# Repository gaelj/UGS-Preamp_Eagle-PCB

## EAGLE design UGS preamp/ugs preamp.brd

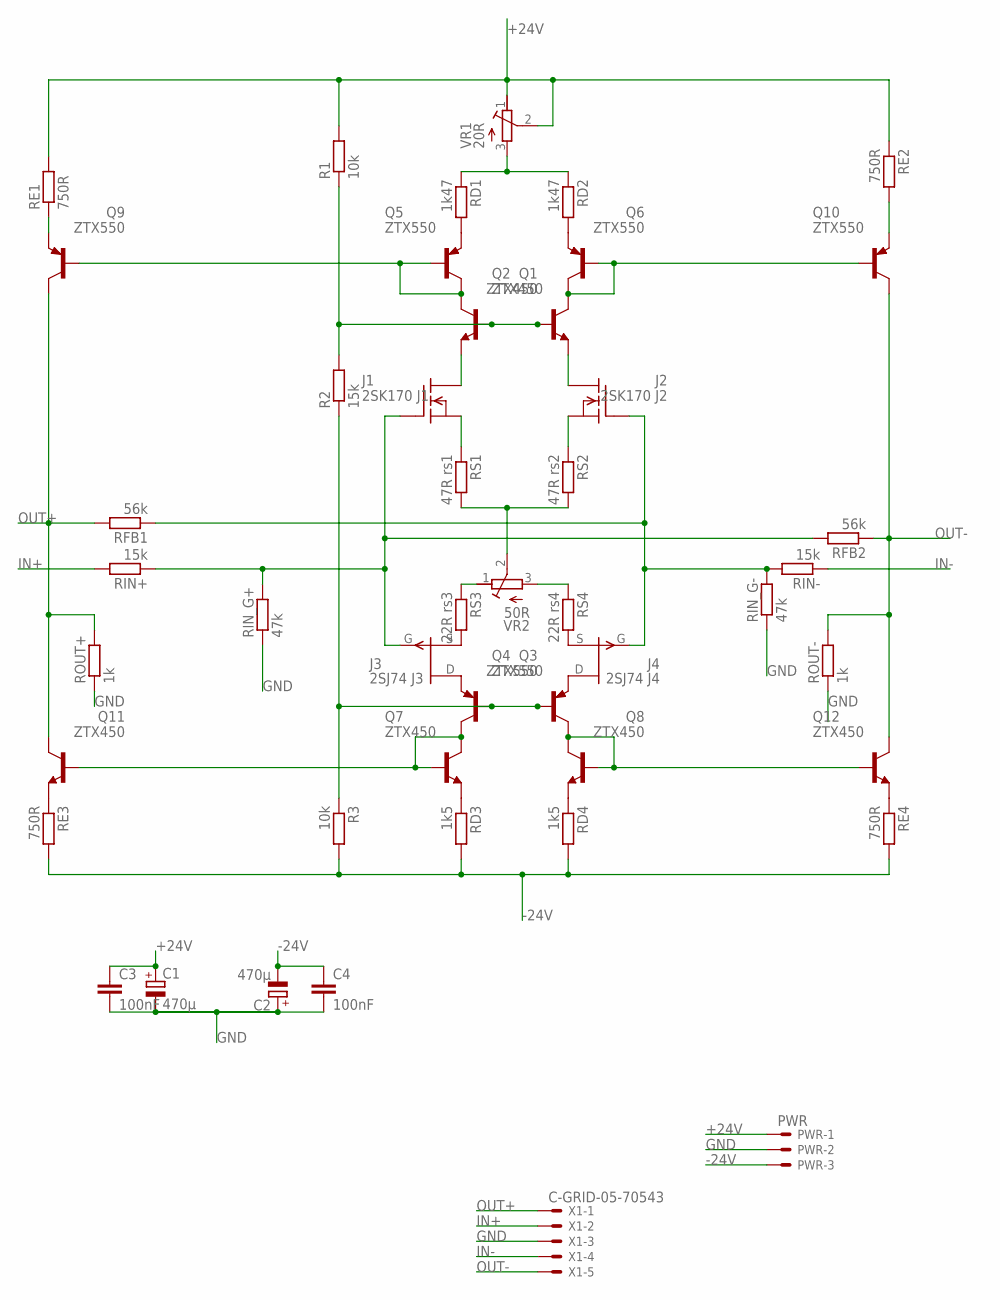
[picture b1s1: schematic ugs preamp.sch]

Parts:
C1, C2: 470µ; E7,5-16
C3, C4: 100nF; C050-025X075
J1: 2SK170 J1; TO92
J2: 2SK170 J2; TO92
J3: 2SJ74 J3; TO92
J4: 2SJ74 J4; TO92
PWR: PWR; 70543-03
Q1, Q2, Q7, Q8, Q11, Q12: ZTX450; TO92-EBC
Q3, Q4, Q5, Q6, Q9, Q10: ZTX550; TO92-EBC
R1, R3: 10k; 0207/10
R2: 15k; 0207/10
RD1, RD2: 1k47; 0207/10
RD3, RD4: 1k5; 0207/10
RE1, RE2, RE3, RE4: 750R; 0207/10
RFB1, RFB2: 56k; 0207/10
RIN+: 15k; 0207/10
RIN-: 15k; 0207/10
RIN_G+: 47k; 0207/10
RIN_G-: 47k; 0207/10
ROUT+: 1k; 0207/10
ROUT-: 1k; 0207/10
RS1: 47R rs1; 0207/10
RS2: 47R rs2; 0207/10
RS3: 22R rs3; 0207/10
RS4: 22R rs4; 0207/10
VR1: 20R; RTRIMT93YA
VR2: 50R; RTRIMT93YA
X1: C-GRID-05-70543; 70543-05

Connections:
+24V: C1.+, C3.1, PWR.1, R1.2, RE1.2, RE2.1, VR1.1 (E), VR1.2 (S)
-24V: C2.-, C4.1, PWR.3, R3.2, RD3.2, RD4.2, RE3.2, RE4.2
GND: C1.-, C2.+, C3.2, C4.2, PWR.2, RIN_G+.1, RIN_G-.1, ROUT+.1, ROUT-.1, X1.3
IN+: RIN+.2, X1.2
IN-: RIN-.1, X1.4
unnamed: J3.3 (D), Q3.E
unnamed: RD1.1, RD2.1, VR1.3 (A)
unnamed: Q1.B, Q2.B, R1.1, R2.2
unnamed: Q3.B, Q4.B, R2.1, R3.1
unnamed: J4.3 (D), Q4.E
unnamed: J4.1 (S), RS4.2
unnamed: J3.1 (S), RS3.2
unnamed: Q10.E, RE2.2
unnamed: J2.2 (G), J4.2 (G), RFB1.1, RIN-.2, RIN_G-.2
unnamed: RS1.2, RS2.2, VR2.2 (S)
unnamed: J2.1 (S), RS2.1
unnamed: Q5.E, RD1.2
unnamed: J1.1 (S), RS1.1
unnamed: RS3.1, VR2.1 (E)
unnamed: RS4.1, VR2.3 (A)
unnamed: J1.2 (G), J3.2 (G), RFB2.2, RIN+.1, RIN_G+.2
unnamed: Q6.E, RD2.2
unnamed: Q11.E, RE3.1
unnamed: Q9.E, RE1.1
unnamed: Q8.E, RD4.1
unnamed: Q4.C, Q8.B, Q8.C, Q12.B
unnamed: Q7.E, RD3.1
unnamed: Q12.E, RE4.1
unnamed: Q2.C, Q6.B, Q6.C, Q10.B
unnamed: Q3.C, Q7.B, Q7.C, Q11.B
unnamed: J1.3 (D), Q1.E
unnamed: J2.3 (D), Q2.E
unnamed: Q1.C, Q5.B, Q5.C, Q9.B
OUT+: Q9.C, Q11.C, RFB1.2, ROUT+.2, X1.1
OUT-: Q10.C, Q12.C, RFB2.1, ROUT-.2, X1.5

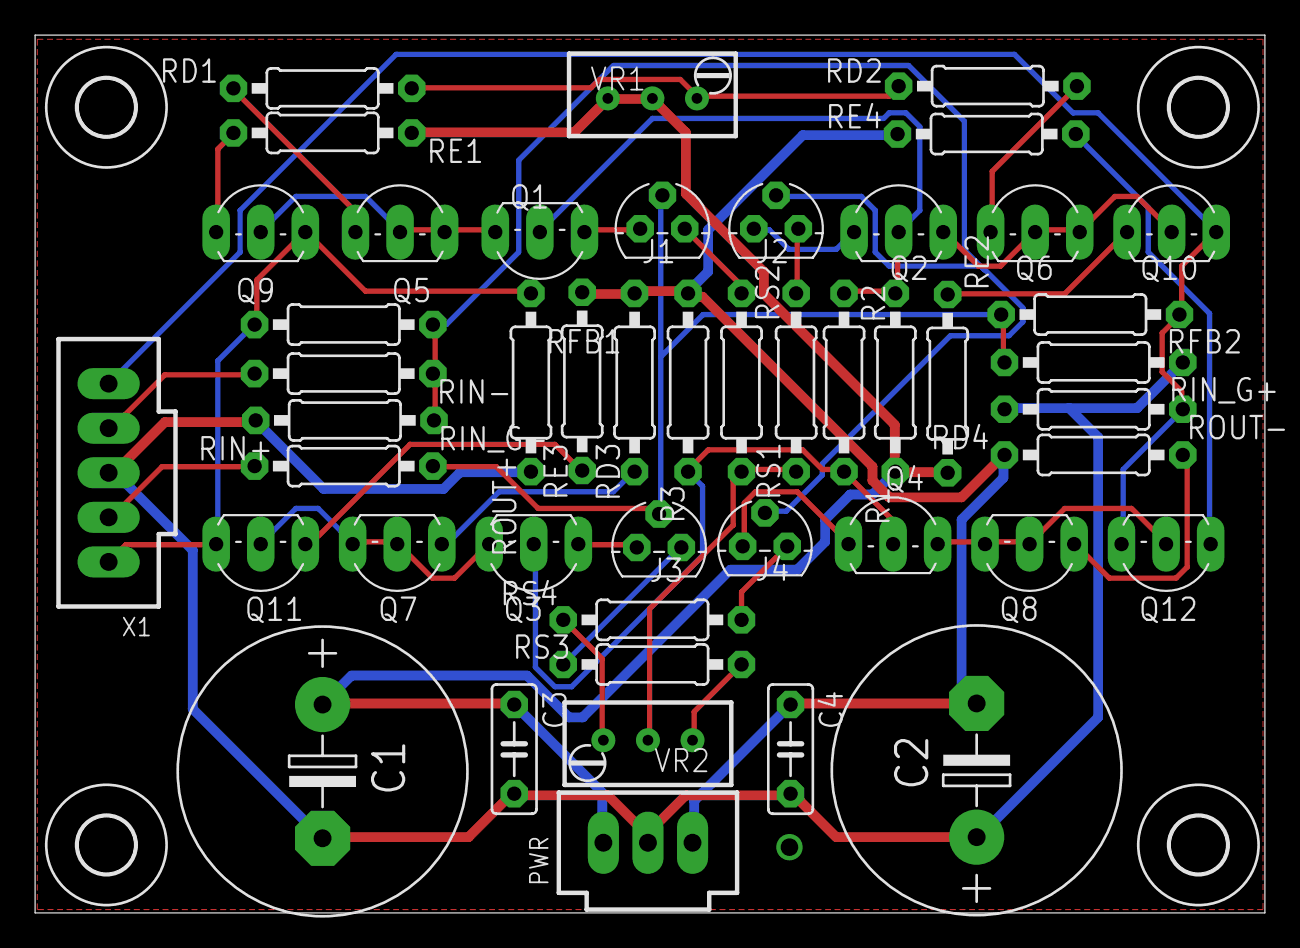
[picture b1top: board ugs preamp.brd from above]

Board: 2 copper layers, 70.1 x 50.0 mm, 51 parts (0 on the bottom side), 35 nets.

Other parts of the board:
U$1, U$2, U$3, U$4: 3,2

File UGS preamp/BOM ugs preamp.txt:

Qty	Value	Device	Package	Parts	Description
2	10k	R-EU_0207/10	0207/10	R1, R3	RESISTOR, European symbol
3	15k	R-EU_0207/10	0207/10	R2, RIN+, RIN-	RESISTOR, European symbol
2	1k	R-EU_0207/10	0207/10	ROUT+, ROUT-	RESISTOR, European symbol
2	1k47	R-EU_0207/10	0207/10	RD1, RD2	RESISTOR, European symbol
2	1k5	R-EU_0207/10	0207/10	RD3, RD4	RESISTOR, European symbol
1	20R	R-TRIMMT93YA	RTRIMT93YA	VR1	Trimm resistor
2	22R	R-EU_0207/10	0207/10	RS3, RS4	RESISTOR, European symbol
2	2SJ74	2N3820	TO92	J3, J4	P-Channel Junction FET
2	2SK170	BSS101	TO92	J1, J2	"N-Channel Enhancement MOSFET 200V; 0,16A; 11Ohm"
2	470µ	CPOL-EUE5-13	E5-13	C1, C2	POLARIZED CAPACITOR, European symbol
2	47R	R-EU_0207/10	0207/10	RS1, RS2	RESISTOR, European symbol
2	47k	R-EU_0207/10	0207/10	RIN_G+, RIN_G-	RESISTOR, European symbol
1	50R	R-TRIMMT93YA	RTRIMT93YA	VR2	Trimm resistor
2	56k	R-EU_0207/10	0207/10	RFB1, RFB2	RESISTOR, European symbol
4	750R	R-EU_0207/10	0207/10	RE1, RE2, RE3, RE4	RESISTOR, European symbol
1	C-GRID-05-70543	C-GRID-05-70543	70543-05	X1	CONNECTOR
1	PWR	C-GRID-03-70543	70543-03	PWR	CONNECTOR
6	ZTX450	-NPN-TO92-EBC	TO92-EBC	Q1, Q2, Q7, Q8, Q11, Q12	NPN Transistror
6	ZTX550	BC328-16-PNP-TO92-EBC	TO92-EBC	Q3, Q4, Q5, Q6, Q9, Q10	PNP Transistror

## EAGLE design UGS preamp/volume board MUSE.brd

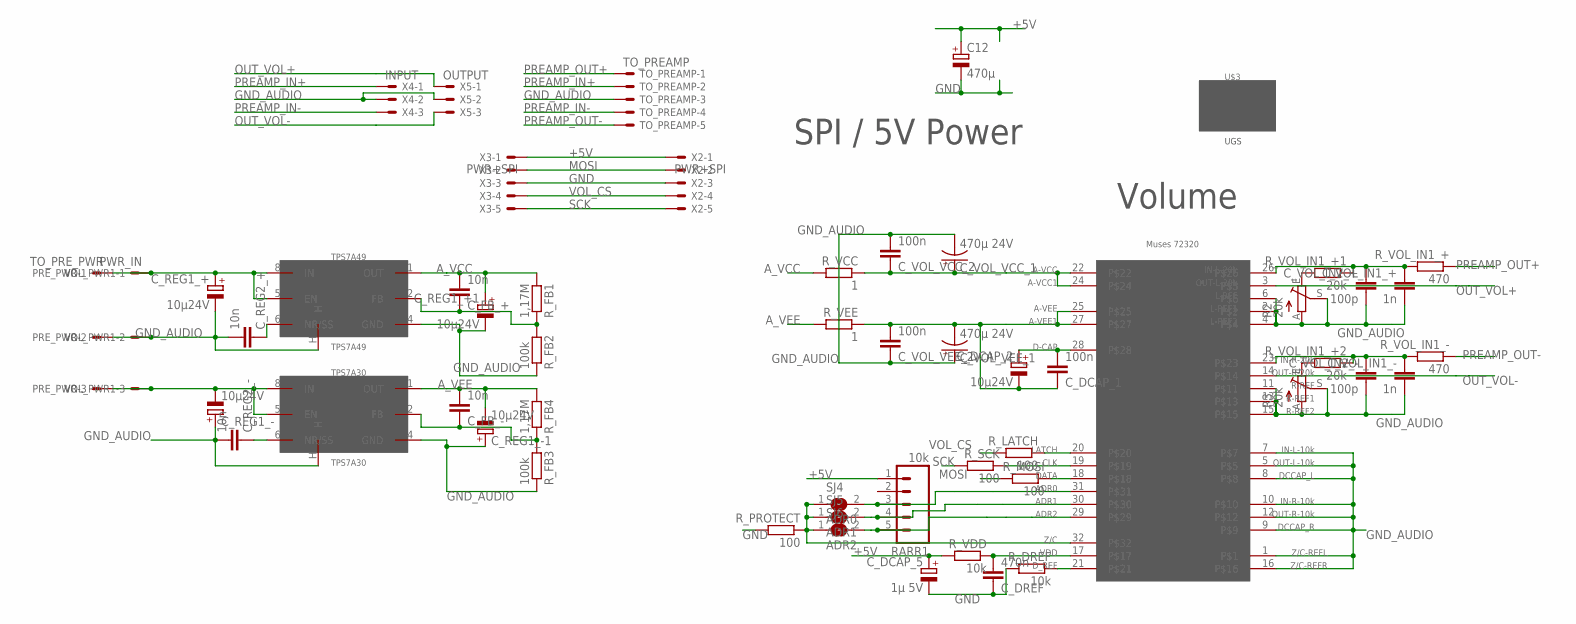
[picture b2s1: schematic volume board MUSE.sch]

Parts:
C12: 470µ; E2,5-6
C_DCAP_1: 100n; C0603
C_DCAP_2: 10µ24V; PANASONIC_C
C_DCAP_5: 1µ 5V; E1,8-4
C_DREF: 470n; C075-042X103
C_FB_+: 10n; C0603
C_FB_-: 10n; C0603
C_REG1_+, C_REG1_+1, C_REG1_-, C_REG1_-1: 10µ24V; PANASONIC_C
C_REG2_+, C_REG2_-: 10n; C0603
C_VOL_IN1_+, C_VOL_IN1_-: 1n; C102-043X133
C_VOL_IN2_+, C_VOL_IN2_-: 100p; C075-032X103
C_VOL_VCC_1: 470µ 24V; PANASONIC_H13
C_VOL_VCC_2: 100n; C0603
C_VOL_VEE_1: 470µ 24V; PANASONIC_H13
C_VOL_VEE_2: 100n; C0603
PRE_PWR: TO_PRE_PWR; 70543-03
R2, R3: 20k; RJ9W
RARR1: 10k; 1X05
R_DREF: 10k; 0207/7
R_FB1, R_FB4: 1,17M; 0207/7
R_FB2, R_FB3: 100k; 0207/7
R_LATCH: 100; 0207/7
R_MOSI: 100; 0207/7
R_PROTECT: 100; 0207/7
R_SCK: 100; 0207/7
R_VCC: 1; 0207/7
R_VDD: 10k; 0207/7
R_VEE: 1; 0207/7
R_VOL_IN1_+, R_VOL_IN1_-: 470; 0207/10
R_VOL_IN1_+1, R_VOL_IN1_+2: 20k; 0207/7
SJ4: ADR0; SJ
SJ5: ADR1; SJ
SJ6: ADR2; SJ
TO_PREAMP: TO_PREAMP; 70543-05
TPS7A30: TPS7A30; MSOP8
TPS7A49: TPS7A49; MSOP8
U$1: MUSES72320; SSOP32
U$3: UGS
VOL_PWR1: PWR_IN; 70543-03
X2, X3: PWR+SPI; 70543-05
X4: INPUT; 70543-03
X5: OUTPUT; 70543-03

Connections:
+5V: C12.+, C_DCAP_5.+, RARR1.1, R_VDD.2, X2.1, X3.1
A_VCC: C_FB_+.2, C_REG1_+1.+, R_FB1.2, R_VCC.2, TPS7A49.1 (OUT)
A_VEE: C_FB_-.2, C_REG1_-1.-, R_FB4.2, R_VEE.2, TPS7A30.1 (OUT)
GND: C12.-, C_DCAP_5.-, C_DREF.1, R_DREF.2, R_PROTECT.2, X2.3, X3.3
GND_AUDIO: C_REG1_+.-, C_REG1_+1.-, C_REG1_-.+, C_REG1_-1.+, C_REG2_+.2, C_REG2_-.2, C_VOL_IN1_+.2, C_VOL_IN1_-.2, C_VOL_IN2_+.2, C_VOL_IN2_-.2, C_VOL_VCC_1.-, C_VOL_VCC_2.2, C_VOL_VEE_1.+, C_VOL_VEE_2.1, PRE_PWR.2, R2.A, R2.S, R3.A, R3.S, R_FB2.1, R_FB3.1, TO_PREAMP.3, TPS7A30.4 (GND), TPS7A30.H, TPS7A49.4 (GND), TPS7A49.H, U$1.1, U$1.2, U$1.4, U$1.5, U$1.6, U$1.7, U$1.8, U$1.9, U$1.10, U$1.11, U$1.12, U$1.13, U$1.15, U$1.16, VOL_PWR1.2, X4.2, X5.2
JHGCD: R_PROTECT.1, SJ4.1, SJ5.1, SJ6.1, U$1.32
MOSI: R_MOSI.2, X2.2, X3.2
unnamed: RARR1.3, SJ4.2, U$1.31
unnamed: RARR1.5, SJ6.2, U$1.29
unnamed: C_REG1_-.-, PRE_PWR.3, TPS7A30.5 (EN), TPS7A30.8 (IN), VOL_PWR1.3
unnamed: C_VOL_IN1_+.1, C_VOL_IN2_+.1, R_VOL_IN1_+.2, R_VOL_IN1_+1.1, U$1.26
unnamed: C_REG1_+.+, PRE_PWR.1, TPS7A49.5 (EN), TPS7A49.8 (IN), VOL_PWR1.1
unnamed: C_VOL_IN1_-.1, C_VOL_IN2_-.1, R_VOL_IN1_+2.1, R_VOL_IN1_-.2, U$1.23
unnamed: R2.E, R_VOL_IN1_+1.2
unnamed: R3.E, R_VOL_IN1_+2.2
unnamed: C_VOL_VCC_1.+, C_VOL_VCC_2.1, R_VCC.1, U$1.22, U$1.24
unnamed: C_DCAP_1.1, C_DCAP_2.-, C_VOL_VEE_1.-, C_VOL_VEE_2.2, R_VEE.1, U$1.25, U$1.27
unnamed: C_DCAP_1.2, C_DCAP_2.+, U$1.28
unnamed: R_LATCH.1, U$1.20
unnamed: R_SCK.1, U$1.19
unnamed: R_MOSI.1, U$1.18
unnamed: RARR1.4, SJ5.2, U$1.30
unnamed: C_DREF.2, R_VDD.1, U$1.17
unnamed: R_DREF.1, U$1.21
unnamed: C_FB_+.1, R_FB1.1, R_FB2.2, TPS7A49.2 (FB)
unnamed: C_FB_-.1, R_FB3.2, R_FB4.1, TPS7A30.2 (FB)
unnamed: C_REG2_-.1, TPS7A30.6 (NR/SS)
unnamed: C_REG2_+.1, TPS7A49.6 (NR/SS)
OUT_VOL+: U$1.3, X5.1
OUT_VOL-: U$1.14, X5.3
PREAMP_IN+: TO_PREAMP.2, X4.1
PREAMP_IN-: TO_PREAMP.4, X4.3
PREAMP_OUT+: R_VOL_IN1_+.1, TO_PREAMP.1
PREAMP_OUT-: R_VOL_IN1_-.1, TO_PREAMP.5
SCK: R_SCK.2, X2.5, X3.5
VOL_CS: R_LATCH.2, X2.4, X3.4

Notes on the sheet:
Volume
SPI / 5V Power

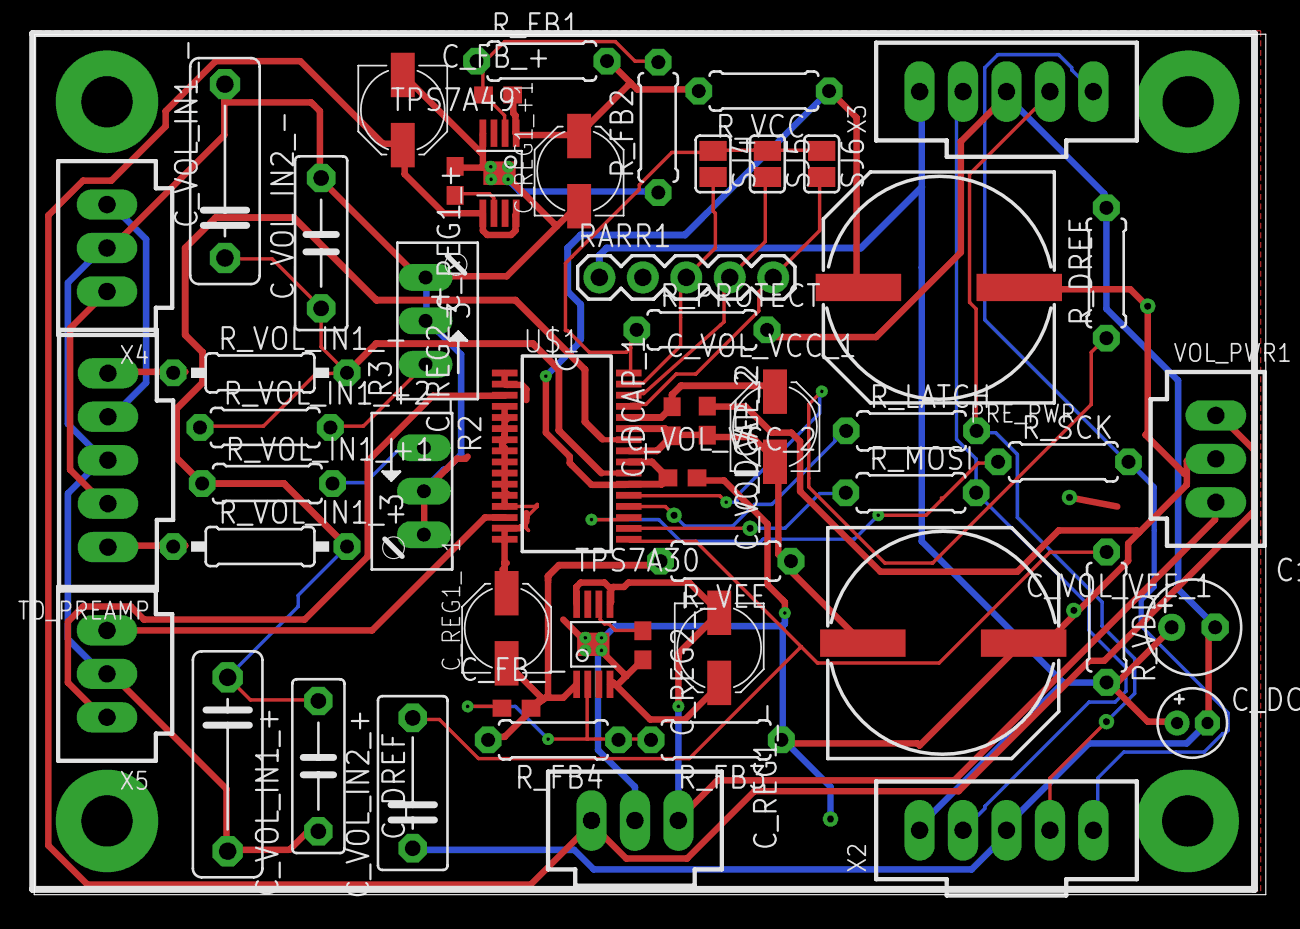
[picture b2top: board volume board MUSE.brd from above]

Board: 2 copper layers, 72.0 x 50.3 mm, 54 parts (0 on the bottom side), 36 nets.

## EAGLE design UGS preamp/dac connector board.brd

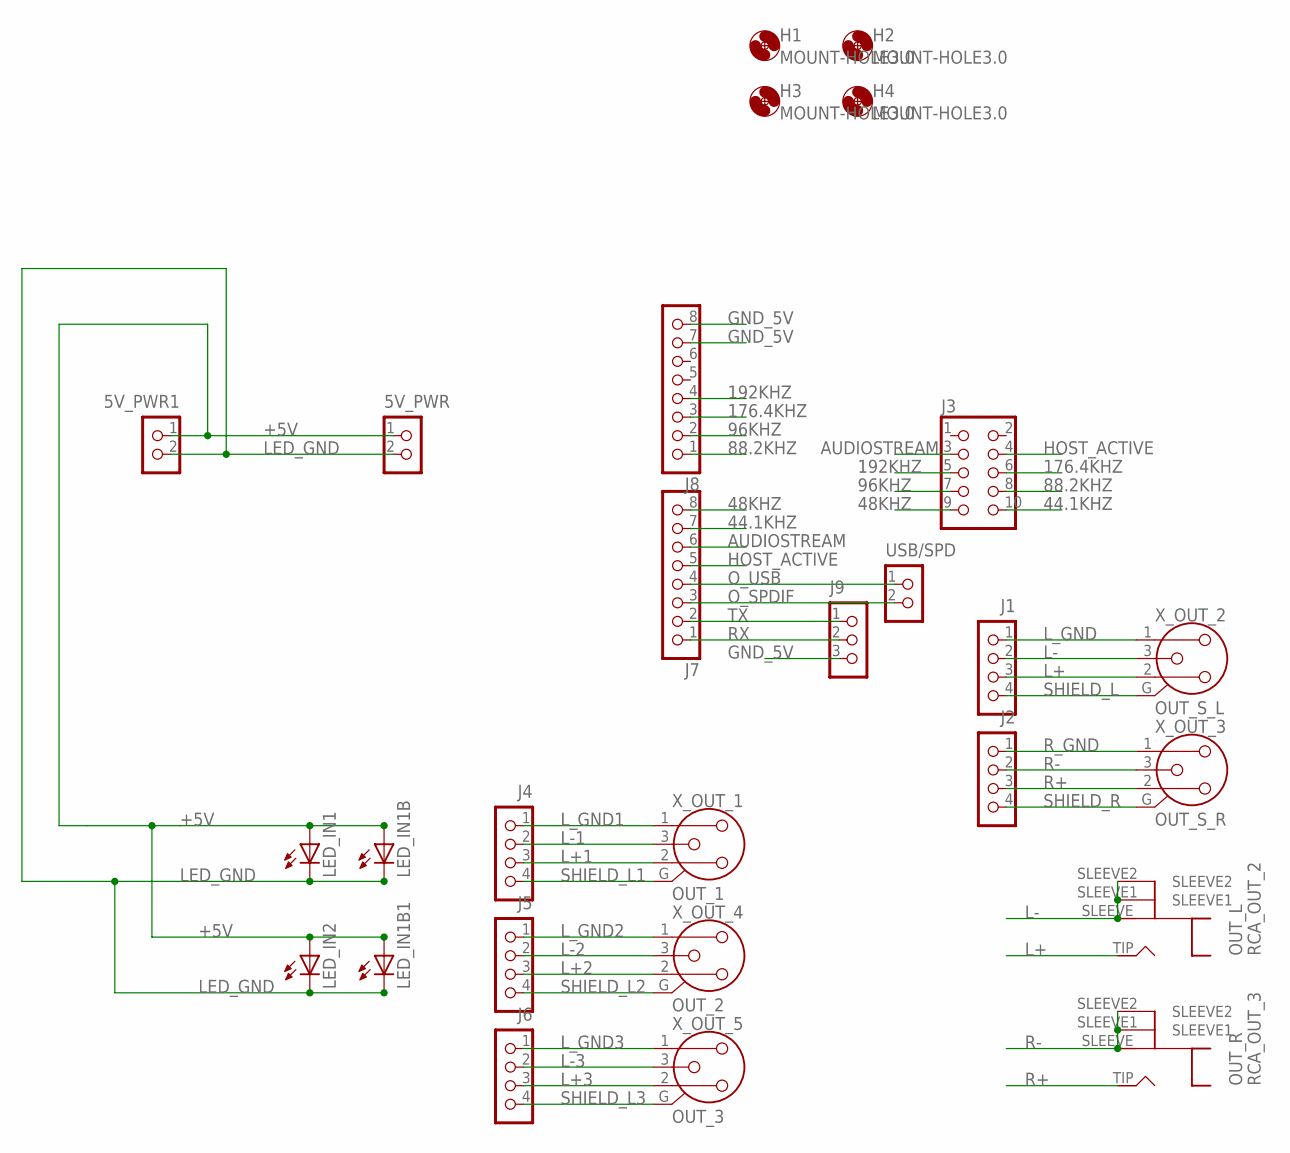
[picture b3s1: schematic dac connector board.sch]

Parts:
5V_PWR, 5V_PWR1: 5V PWR; M1X2
H1, H2, H3, H4: MOUNT-HOLE3.0; 3,0
J1, J2: CON_HEADER_1X04; M1X4
J3: DAC; M2X5
J4: CON_OUT_1; M1X4
J5: CON_OUT_2; M1X4
J6: CON_OUT_3; M1X4
J7: ARD1; M1X8
J8: ARD2; M1X8
J9: SERIAL; M1X3
LED_IN1, LED_IN1B, LED_IN1B1, LED_IN2: TLLG4400; LED3MM
RCA_OUT_2: OUT_L; MONO_JACK
RCA_OUT_3: OUT_R; MONO_JACK
USB/SPD: IN_SEL; M1X2
X_OUT_1: OUT_1; NC3MBH; MPN NC3MBH
X_OUT_2: OUT_S_L; NC3MBH; MPN NC3MBH
X_OUT_3: OUT_S_R; NC3MBH; MPN NC3MBH
X_OUT_4: OUT_2; NC3MBH; MPN NC3MBH
X_OUT_5: OUT_3; NC3MBH; MPN NC3MBH

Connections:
44.1KHZ: J3.10, J7.7
48KHZ: J3.9, J7.8
88.2KHZ: J3.8, J8.1
96KHZ: J3.7, J8.2
176.4KHZ: J3.6, J8.3
192KHZ: J3.5, J8.4
+5V: 5V_PWR.1, 5V_PWR1.1, LED_IN1.A, LED_IN1B.A, LED_IN1B1.A, LED_IN2.A
AUDIOSTREAM: J3.3, J7.6
GND_5V: J8.7, J8.8, J9.3
HOST_ACTIVE: J3.4, J7.5
L+: J1.3, RCA_OUT_2.TIP, X_OUT_2.2
L+1: J4.3, X_OUT_1.2
L+2: J5.3, X_OUT_4.2
L+3: J6.3, X_OUT_5.2
L-: J1.2, RCA_OUT_2.SLEEVE, RCA_OUT_2.SLEEVE1, RCA_OUT_2.SLEEVE2, X_OUT_2.3
L-1: J4.2, X_OUT_1.3
L-2: J5.2, X_OUT_4.3
L-3: J6.2, X_OUT_5.3
LED_GND: 5V_PWR.2, 5V_PWR1.2, LED_IN1.K (C), LED_IN1B.K (C), LED_IN1B1.K (C), LED_IN2.K (C)
L_GND: J1.1, X_OUT_2.1
L_GND1: J4.1, X_OUT_1.1
L_GND2: J5.1, X_OUT_4.1
L_GND3: J6.1, X_OUT_5.1
O_SPDIF: J7.3, USB/SPD.2
O_USB: J7.4, USB/SPD.1
R+: J2.3, RCA_OUT_3.TIP, X_OUT_3.2
R-: J2.2, RCA_OUT_3.SLEEVE, RCA_OUT_3.SLEEVE1, RCA_OUT_3.SLEEVE2, X_OUT_3.3
RX: J7.1, J9.2
R_GND: J2.1, X_OUT_3.1
SHIELD_L: J1.4, X_OUT_2.G
SHIELD_L1: J4.4, X_OUT_1.G
SHIELD_L2: J5.4, X_OUT_4.G
SHIELD_L3: J6.4, X_OUT_5.G
SHIELD_R: J2.4, X_OUT_3.G
TX: J7.2, J9.1

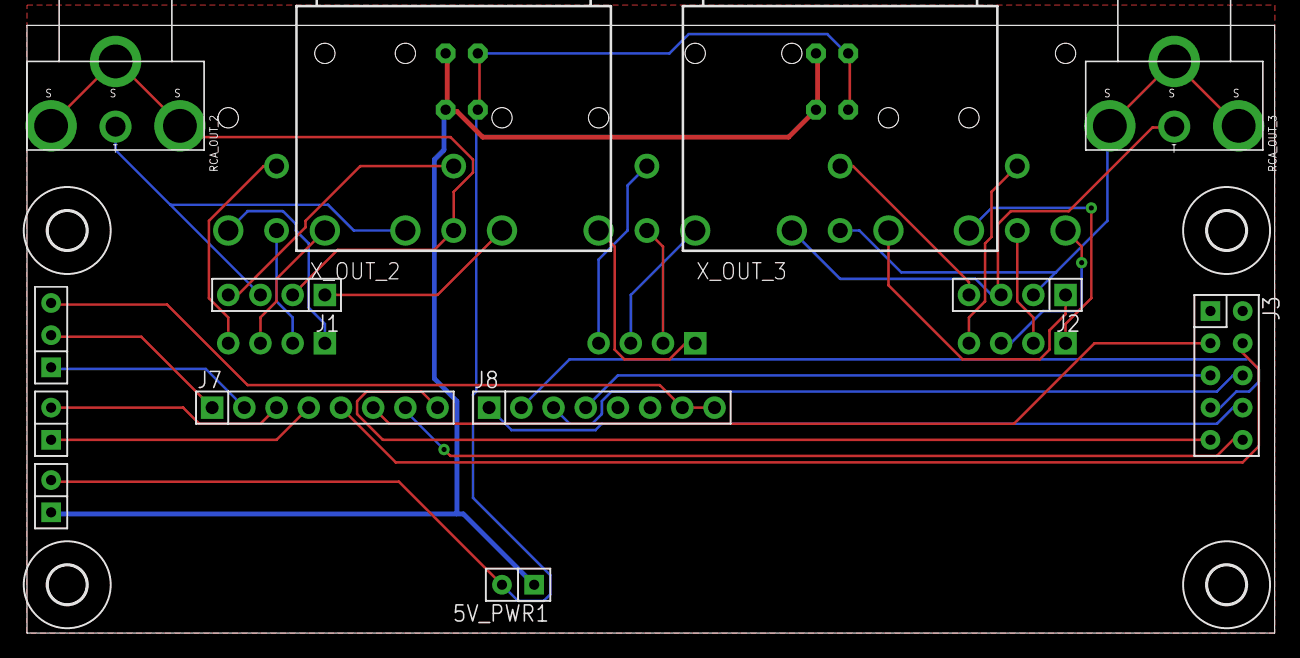
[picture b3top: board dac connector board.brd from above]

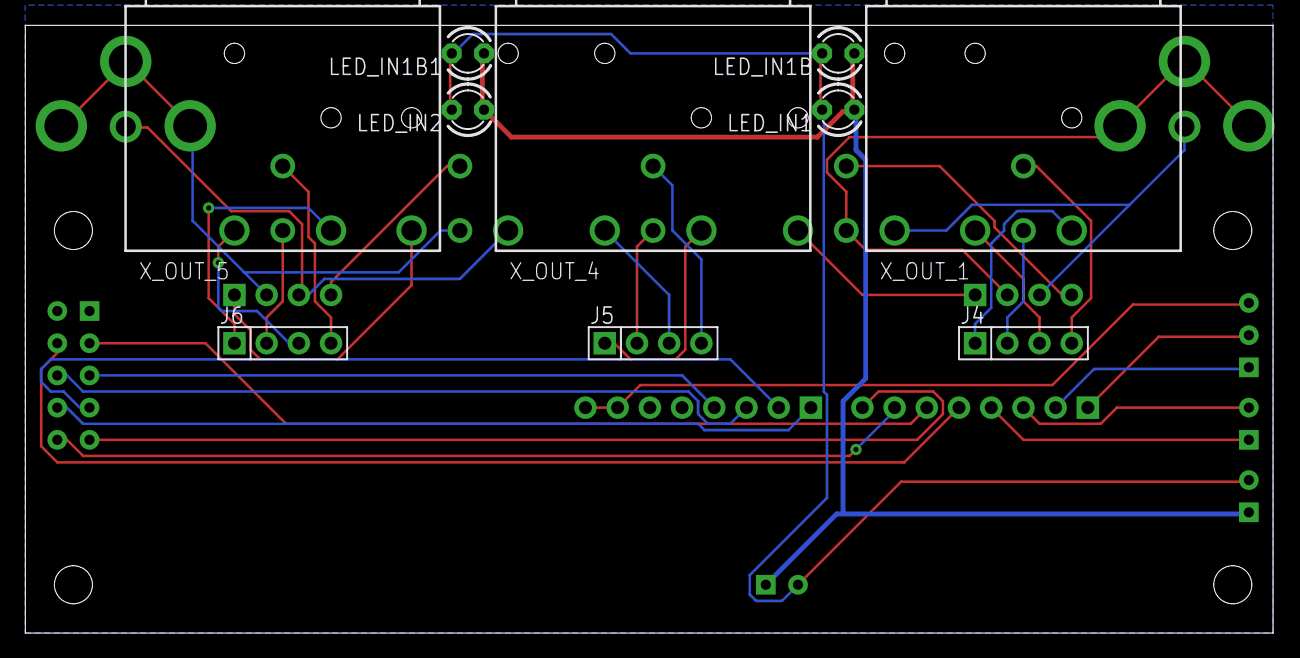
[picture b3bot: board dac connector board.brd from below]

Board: 2 copper layers, 98.4 x 47.9 mm, 27 parts (10 on the bottom side), 35 nets.

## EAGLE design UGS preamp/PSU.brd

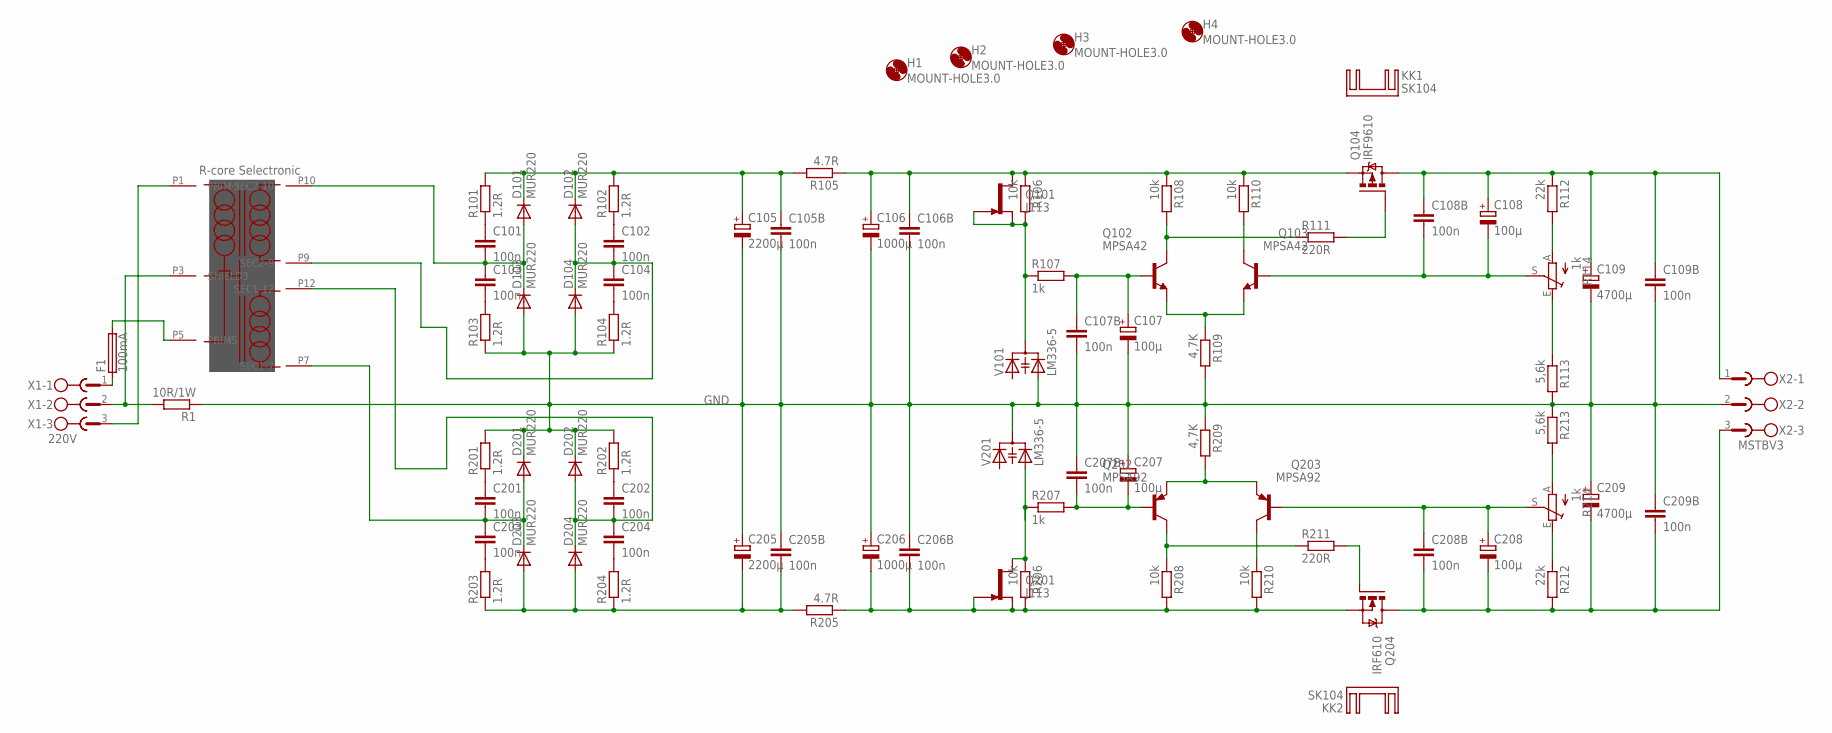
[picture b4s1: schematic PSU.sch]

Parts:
C101, C102, C103, C104, C105B, C106B, C107B, C108B, C109B, C201, C202, C203, C204, C205B, C206B, C207B, C208B, C209B: 100n; C050-025X075
C105, C205: 2200µ; E7,5-16
C106, C206: 1000µ; E7,5-16
C107, C108, C207, C208: 100µ; E5-10,5
C109, C209: 4700µ; EB25D
D101, D102, D103, D104, D201, D202, D203, D204: MUR220; DO201-15
F1: 100mA; GSH15
H1, H2, H3, H4: MOUNT-HOLE3.0; 3,0
KK1, KK2: SK104
Q101, Q201: J113; TO-92
Q102, Q103: MPSA42; TO92-EBC
Q104: IRF9610; TO220BV
Q202, Q203: MPSA92; TO92-EBC
Q204: IRF610; TO220BV
R1: 10R/1W; P0613/15
R101, R102, R103, R104, R201, R202, R203, R204: 1.2R; 0207/10
R105, R205: 4.7R; 0207/10
R106, R108, R110, R206, R208, R210: 10k; 0207/10
R107, R207: 1k; 0207/10
R109, R209: 4,7K; 0207/10
R111, R211: 220R; 0207/10
R112, R212: 22k; 0207/10
R113, R213: 5,6k; 0207/10
R114, R214: 1k; S64W
U$1: R-CORE-SELECTRONIC-PCB; R-CORE48MM
V101, V201: LM336-5; SOT54E
X1: 220V; MSTBV3
X2: MSTBV3

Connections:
GND: C105.-, C105B.2, C106.-, C106B.2, C107.-, C107B.2, C109.-, C109B.2, C205.+, C205B.1, C206.+, C206B.1, C207.+, C207B.1, C209.+, C209B.1, D103.A, D104.A, D201.C, D202.C, R1.1, R103.1, R104.1, R109.2, R113.2, R201.2, R202.2, R209.1, R213.1, V101.A2, V201.C, X2.2
unnamed: C101.2, C103.1, D101.A, D103.C, U$1.P10 (SEC2-10)
unnamed: C102.2, C104.1, D102.A, D104.C, U$1.P9 (SEC2-9)
unnamed: C102.1, R102.1
unnamed: C103.2, R103.2
unnamed: C106.+, C106B.1, Q101.1 (D), Q104.S, R105.1, R106.1, R108.1, R110.1
unnamed: C101.1, R101.1
unnamed: C104.2, R104.2
unnamed: C105.+, C105B.1, D101.C, D102.C, R101.2, R102.2, R105.2
unnamed: C206.-, C206B.2, Q201.2 (S), Q201.3 (G), Q204.S, R205.1, R206.2, R208.2, R210.2
unnamed: C201.2, C203.1, D201.A, D203.C, U$1.P7 (SEC1-7)
unnamed: C202.2, C204.1, D202.A, D204.C, U$1.P12 (SEC1-12)
unnamed: C201.1, R201.1
unnamed: C202.1, R202.1
unnamed: C203.2, R203.2
unnamed: C204.2, R204.2
unnamed: C208.-, C208B.2, C209.-, C209B.2, Q204.D, R212.2, X2.3
unnamed: C205.-, C205B.2, D203.A, D204.A, R203.1, R204.1, R205.2
unnamed: F1.1, X1.1
unnamed: Q201.1 (D), R206.1, R207.1, V201.A2
unnamed: Q104.G, R111.2
unnamed: Q102.C, R108.2, R111.1
unnamed: Q202.C, R208.1, R211.1
unnamed: C107.+, C107B.1, Q102.B, R107.2
unnamed: C207.-, C207B.2, Q202.B, R207.2
unnamed: Q103.C, R110.2
unnamed: Q102.E, Q103.E, R109.1
unnamed: Q202.E, Q203.E, R209.2
unnamed: Q203.C, R210.1
unnamed: C108.+, C108B.1, C109.+, C109B.1, Q104.D, R112.1, X2.1
unnamed: Q101.2 (S), Q101.3 (G), R106.2, R107.1, V101.C
unnamed: Q204.G, R211.2
unnamed: C108.-, C108B.2, Q103.B, R114.S
unnamed: C208.+, C208B.1, Q203.B, R214.S
unnamed: R112.2, R114.A
unnamed: R113.1, R114.E
unnamed: R212.1, R214.E
unnamed: R213.2, R214.A
unnamed: F1.2, U$1.P5 (PRIM5)
unnamed: U$1.P1 (PRIM-1), X1.3
unnamed: R1.2, U$1.P3 (SHIELD3), X1.2

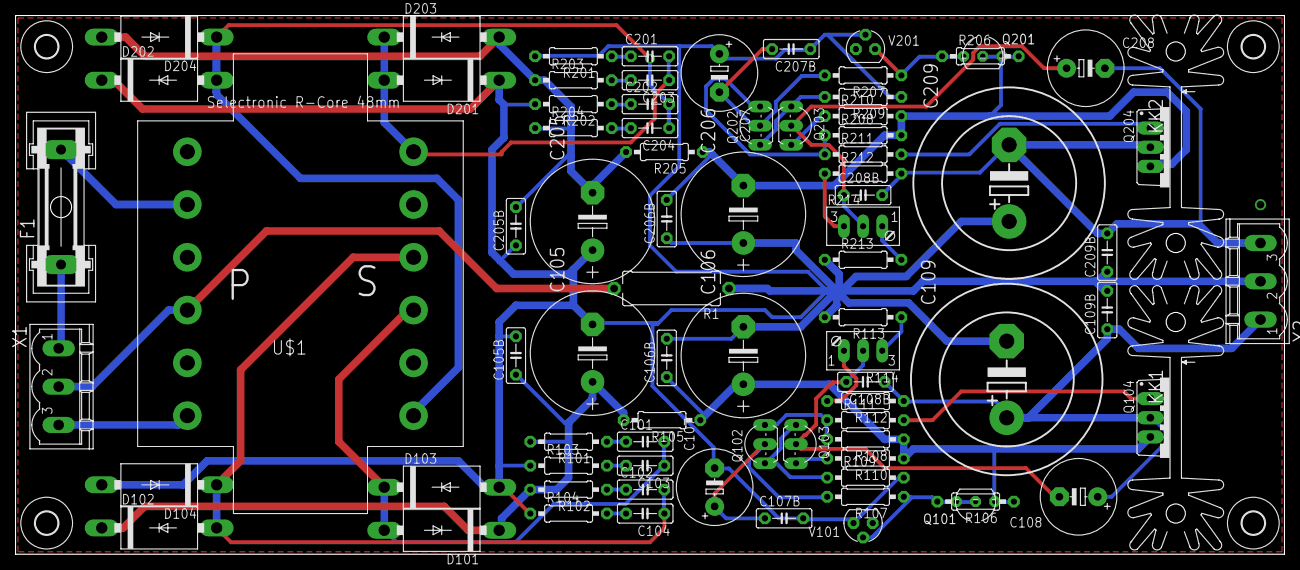
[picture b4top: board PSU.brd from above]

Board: 2 copper layers, 168.3 x 71.4 mm, 85 parts (0 on the bottom side), 41 nets.

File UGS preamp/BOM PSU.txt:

Partlist exported from J:/eagle/UGS preamp/PSU.sch at 18/01/2015 17:40:55

Qty Value                  Device                   Package      Parts                                                                                                                Description                                            
1                          22-23-2031               22-23-2031   X3                                                                                                                   .100" (2.54mm) Center Header - 3 Pin                   
8   1.2R                   R-EU_0207/10             0207/10      R101, R102, R103, R104, R201, R202, R203, R204                                                                       RESISTOR, European symbol                              
2   1000µ                  CPOL-EUE10-25            EB25D        C106, C206                                                                                                           POLARIZED CAPACITOR, European symbol                   
1   100mA                  GSH15                    GSH15        F1                                                                                                                   FUSE HOLDER                                            
18  100n                   C-EU050-025X075          C050-025X075 C101, C102, C103, C104, C105B, C106B, C107B, C108B, C109B, C201, C202, C203, C204, C205B, C206B, C207B, C208B, C209B CAPACITOR, European symbol                             
4   100µ                   CPOL-EUE5-10.5           E5-10,5      C107, C108, C207, C208                                                                                               POLARIZED CAPACITOR, European symbol                   
1   10R/1W                 R-EU_0613/15             P0613/15     R1                                                                                                                   RESISTOR, European symbol                              
6   10k                    R-EU_0207/10             0207/10      R106, R108, R110, R206, R208, R210                                                                                   RESISTOR, European symbol                              
2   1k                     R-EU_0207/10             0207/10      R107, R207                                                                                                           RESISTOR, European symbol                              
2   1k                     TRIM_EU-S64W             S64W         R114, R214                                                                                                           POTENTIOMETER                                          
2   2200µ                  CPOL-EUE10-25            EB25D        C105, C205                                                                                                           POLARIZED CAPACITOR, European symbol                   
2   220R                   R-EU_0207/10             0207/10      R111, R211                                                                                                           RESISTOR, European symbol                              
1   220V                   MSTBV3                   MSTBV3       X1                                                                                                                   PHOENIX                                                
2   22k                    R-EU_0207/10             0207/10      R112, R212                                                                                                           RESISTOR, European symbol                              
2   4,7K                   R-EU_0207/10             0207/10      R109, R209                                                                                                           RESISTOR, European symbol                              
2   4.7R                   R-EU_0309/10             0309/10      R105, R205                                                                                                           RESISTOR, European symbol                              
2   4700µ                  CPOL-EUE10-25            EB25D        C109, C209                                                                                                           POLARIZED CAPACITOR, European symbol                   
2   5,6k                   R-EU_0207/10             0207/10      R113, R213                                                                                                           RESISTOR, European symbol                              
1   IRF610                 IRF740                   TO220BV      Q204                                                                                                                 N-CHANNEL MOS FET                                      
1   IRF9610                IRF9530                  TO220BV      Q104                                                                                                                 P-CHANNEL HEXFET POWER-MOS-FET                         
2   J113                   2N5458                   TO-92        Q101, Q201                                                                                                                                                                  
2   LM336-5                DIODE-2CAPACITANCESOT54E SOT54E       V101, V201                                                                                                           Capacity DIODE                                         
4   MOUNT-HOLE3.0          MOUNT-HOLE3.0            3,0          H1, H2, H3, H4                                                                                                       MOUNTING HOLE with drill center marker                 
2   MPSA42                 -NPN-TO92-EBC            TO92-EBC     Q102, Q103                                                                                                           NPN Transistror                                        
2   MPSA92                 BCX58-PNP-TO92-EBC       TO92-EBC     Q202, Q203                                                                                                           PNP Transistror                                        
8   MUR220                 BY500                    DO201-15     D101, D102, D103, D104, D201, D202, D203, D204                                                                       DIODE                                                  
1   R-CORE-SELECTRONIC-PCB R-CORE-SELECTRONIC-PCB   R-CORE48MM   U$1                                                                                                                  Transformateurs R-core pour PCB vendus par Selectronic 
2   SK104                  SK104                    SK104        KK1, KK2                                                                                                             HEATSINK manufacturer Fischer/distributor Buerklin

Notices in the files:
parts and their libraries:
SparkFun: Licensing: CC v3.0 Share-Alike You are welcome to use this library for commercial purposes.
